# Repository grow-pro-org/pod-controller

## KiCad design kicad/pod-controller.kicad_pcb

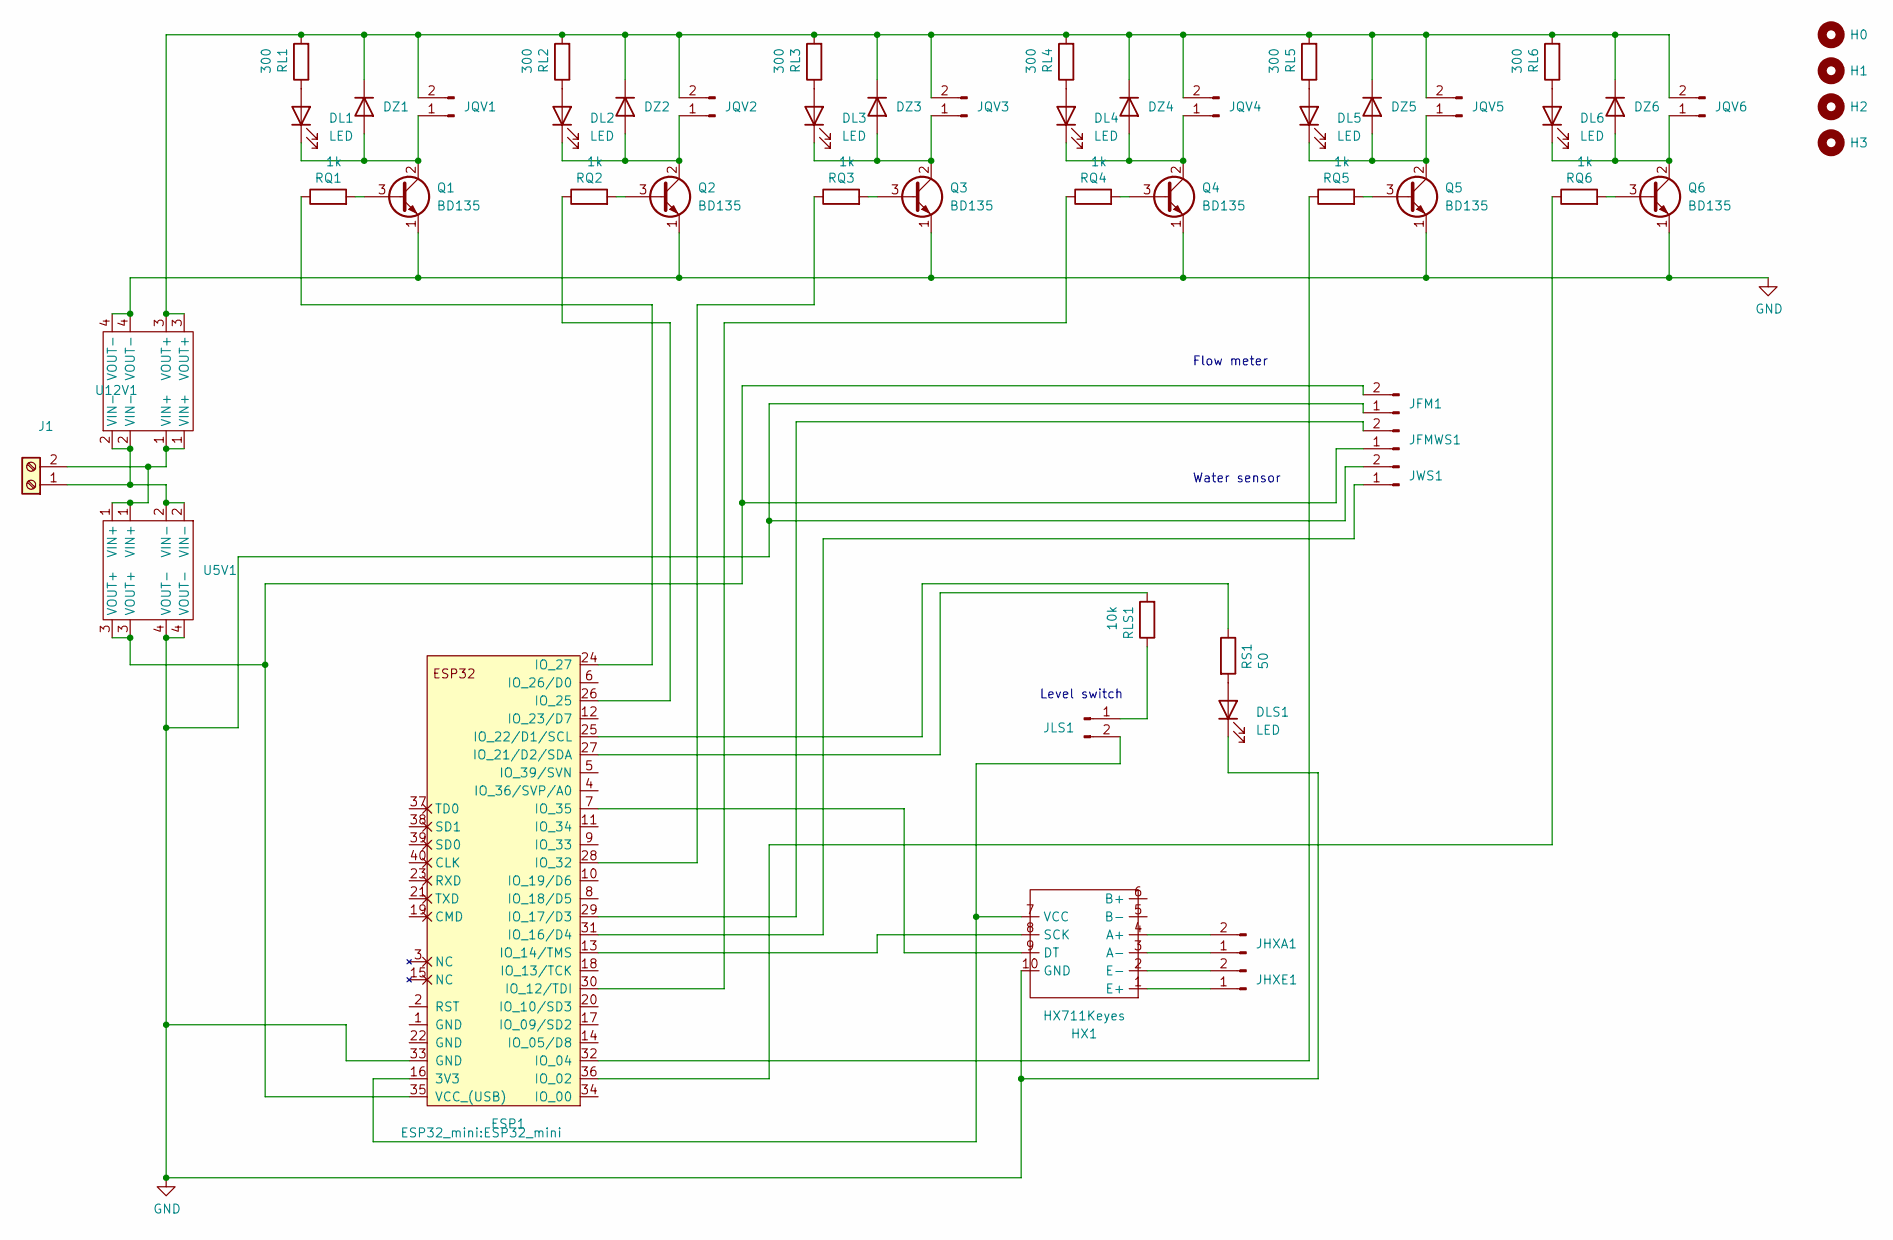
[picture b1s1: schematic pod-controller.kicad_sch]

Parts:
DL1, DL2, DL3, DL4, DL5, DL6: LED; D_1206_3216Metric
DLS1: LED; D_1206_3216Metric
DZ1, DZ2, DZ3, DZ4, DZ5, DZ6: 1N914; D_SMA
ESP1: mini_esp32; ESP32_mini
H0, H1, H2, H3: MountingHole; MountingHole_2.2mm_M2
HX1: HX711Keyes; HX711
J1: Screw_Terminal_01x02; TerminalBlock_bornier-2_P5.08mm
JFM1: Conn_01x02_Male; JST_EH_B2B-EH-A_1x02_P2.50mm_Vertical
JFMWS1: Conn_01x02_Male; JST_EH_B2B-EH-A_1x02_P2.50mm_Vertical
JHXA1: Conn_01x02_Male; JST_EH_B2B-EH-A_1x02_P2.50mm_Vertical
JHXE1: Conn_01x02_Male; JST_EH_B2B-EH-A_1x02_P2.50mm_Vertical
JLS1: Conn_01x02_Male; JST_EH_B2B-EH-A_1x02_P2.50mm_Vertical
JQV1, JQV2, JQV3, JQV4, JQV5, JQV6: Conn_01x02_Male; JST_EH_B2B-EH-A_1x02_P2.50mm_Vertical
JWS1: Conn_01x02_Male; JST_EH_B2B-EH-A_1x02_P2.50mm_Vertical
Q1, Q2, Q3, Q4, Q5, Q6: BD135; TO-126-3_Vertical
RL1, RL2, RL3, RL4, RL5, RL6: 300; R_0805_2012Metric
RLS1: 10k; R_0805_2012Metric
RQ1, RQ2, RQ3, RQ4, RQ5, RQ6: 1k; R_0805_2012Metric
RS1: 50; R_0805_2012Metric
U5V1, U12V1: MPT1584EN; SRT_MPT1584EN_Module

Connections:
GND: DLS1.1 (K), ESP1.33 (GND), HX1.10 (GND), JFM1.1, JWS1.2, Q1.1 (E), Q2.1 (E), Q3.1 (E), Q4.1 (E), Q5.1 (E), Q6.1 (E), U5V1.4 (VOUT-), U12V1.4 (VOUT-)
unnamed: DL1.1 (K), DZ1.2 (A), JQV1.1, Q1.2 (C)
unnamed: DL1.2 (A), RL1.1
unnamed: DL2.1 (K), DZ2.2 (A), JQV2.1, Q2.2 (C)
unnamed: DL2.2 (A), RL2.1
unnamed: DL3.1 (K), DZ3.2 (A), JQV3.1, Q3.2 (C)
unnamed: DL3.2 (A), RL3.1
unnamed: DL4.1 (K), DZ4.2 (A), JQV4.1, Q4.2 (C)
unnamed: DL4.2 (A), RL4.1
unnamed: DL5.1 (K), DZ5.2 (A), JQV5.1, Q5.2 (C)
unnamed: DL5.2 (A), RL5.1
unnamed: DL6.1 (K), DZ6.2 (A), JQV6.1, Q6.2 (C)
unnamed: DL6.2 (A), RL6.1
unnamed: DLS1.2 (A), RS1.2
unnamed: DZ1.1 (K), DZ2.1 (K), DZ3.1 (K), DZ4.1 (K), DZ5.1 (K), DZ6.1 (K), JQV1.2, JQV2.2, JQV3.2, JQV4.2, JQV5.2, JQV6.2, RL1.2, RL2.2, RL3.2, RL4.2, RL5.2, RL6.2, U12V1.3 (VOUT+)
unnamed: ESP1.7 (IO_35), HX1.9 (DT)
unnamed: ESP1.13 (IO_14/TMS), HX1.8 (SCK)
unnamed: ESP1.16 (3V3), HX1.7 (VCC), JLS1.2
unnamed: ESP1.24 (IO_27), RQ1.1
unnamed: ESP1.25 (IO_22/D1/SCL), RS1.1
unnamed: ESP1.26 (IO_25), RQ2.1
unnamed: ESP1.27 (IO_21/D2/SDA), RLS1.2
unnamed: ESP1.28 (IO_32), RQ3.1
unnamed: ESP1.29 (IO_17/D3), JFMWS1.2
unnamed: ESP1.30 (IO_12/TDI), RQ4.1
unnamed: ESP1.31 (IO_16/D4), JWS1.1
unnamed: ESP1.32 (IO_04), RQ5.1
unnamed: ESP1.35 (VCC_(USB)), JFM1.2, JFMWS1.1, U5V1.3 (VOUT+)
unnamed: ESP1.36 (IO_02), RQ6.1
unnamed: HX1.1 (E+), JHXE1.1
unnamed: HX1.2 (E-), JHXE1.2
unnamed: HX1.3 (A-), JHXA1.1
unnamed: HX1.4 (A+), JHXA1.2
unnamed: J1.1, U5V1.2 (VIN-), U12V1.2 (VIN-)
unnamed: J1.2, U5V1.1 (VIN+), U12V1.1 (VIN+)
unnamed: JLS1.1, RLS1.1
unnamed: Q1.3 (B), RQ1.2
unnamed: Q2.3 (B), RQ2.2
unnamed: Q3.3 (B), RQ3.2
unnamed: Q4.3 (B), RQ4.2
unnamed: Q5.3 (B), RQ5.2
unnamed: Q6.3 (B), RQ6.2

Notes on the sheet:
Flow meter
Level switch
Water sensor

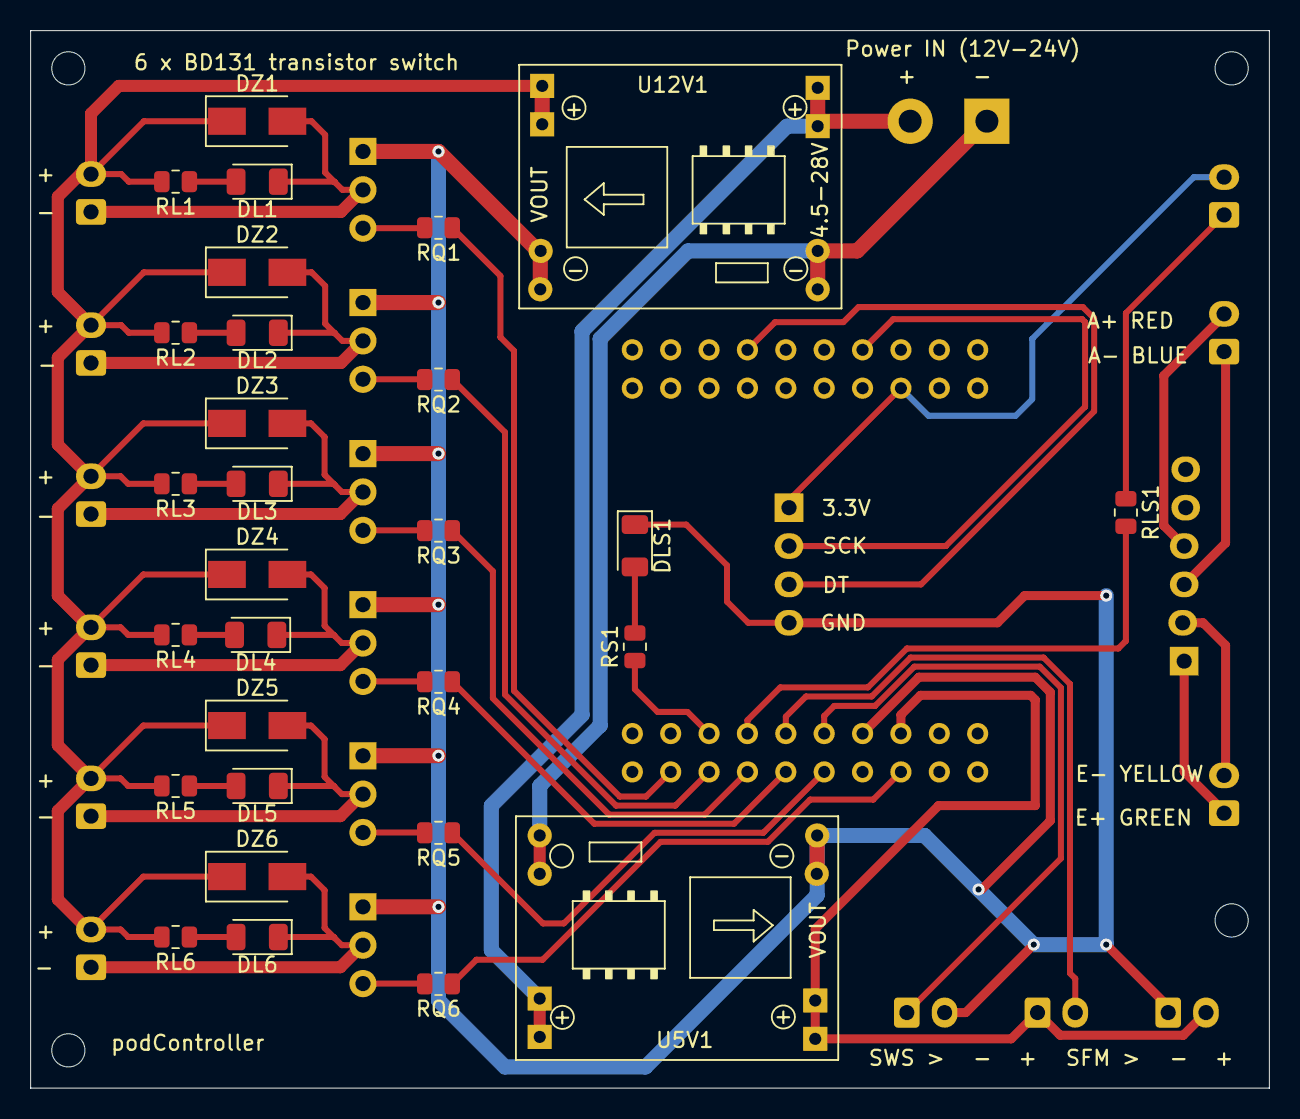
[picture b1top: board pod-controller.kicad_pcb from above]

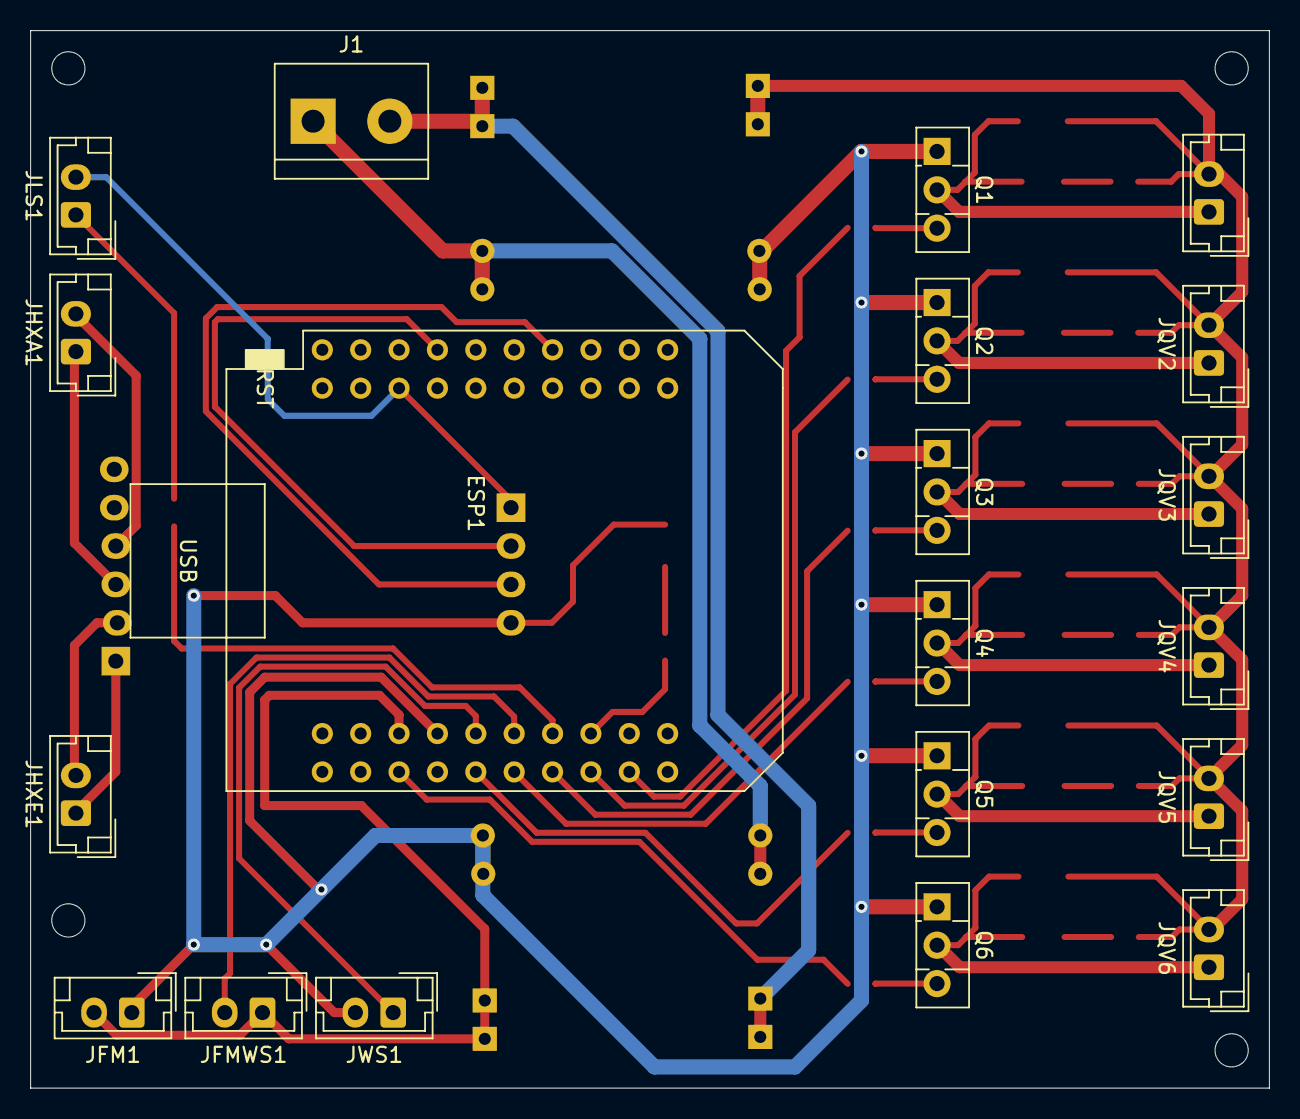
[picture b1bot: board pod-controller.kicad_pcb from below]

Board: 2 copper layers, 82.0 x 70.0 mm, 54 parts (20 on the bottom side), 42 nets.

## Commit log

2022-03-21 Inital commit
2022-03-21 Added corresponding kicad files
